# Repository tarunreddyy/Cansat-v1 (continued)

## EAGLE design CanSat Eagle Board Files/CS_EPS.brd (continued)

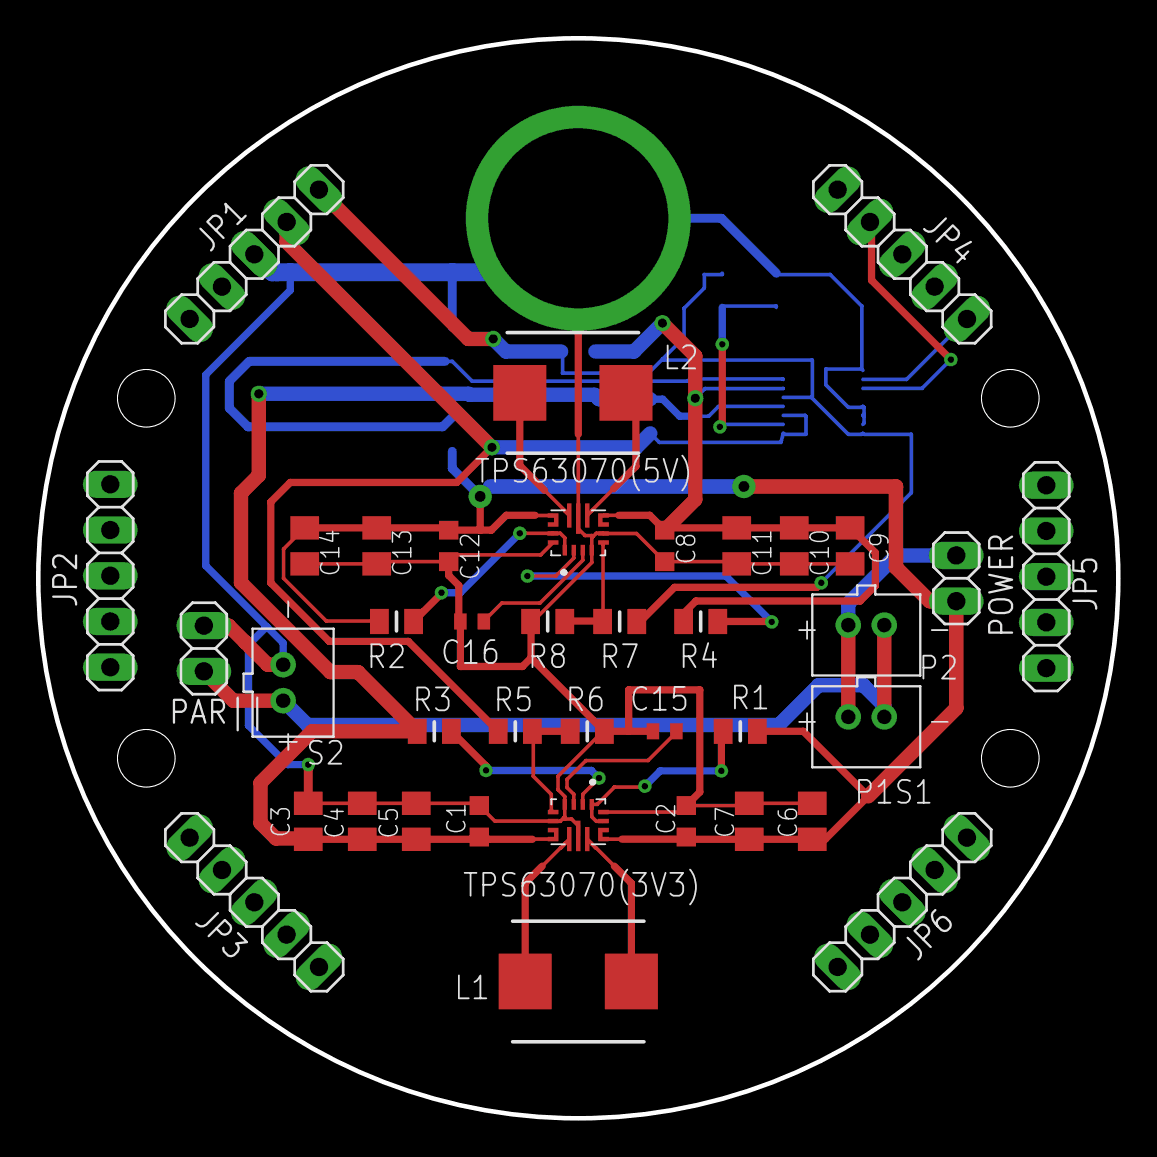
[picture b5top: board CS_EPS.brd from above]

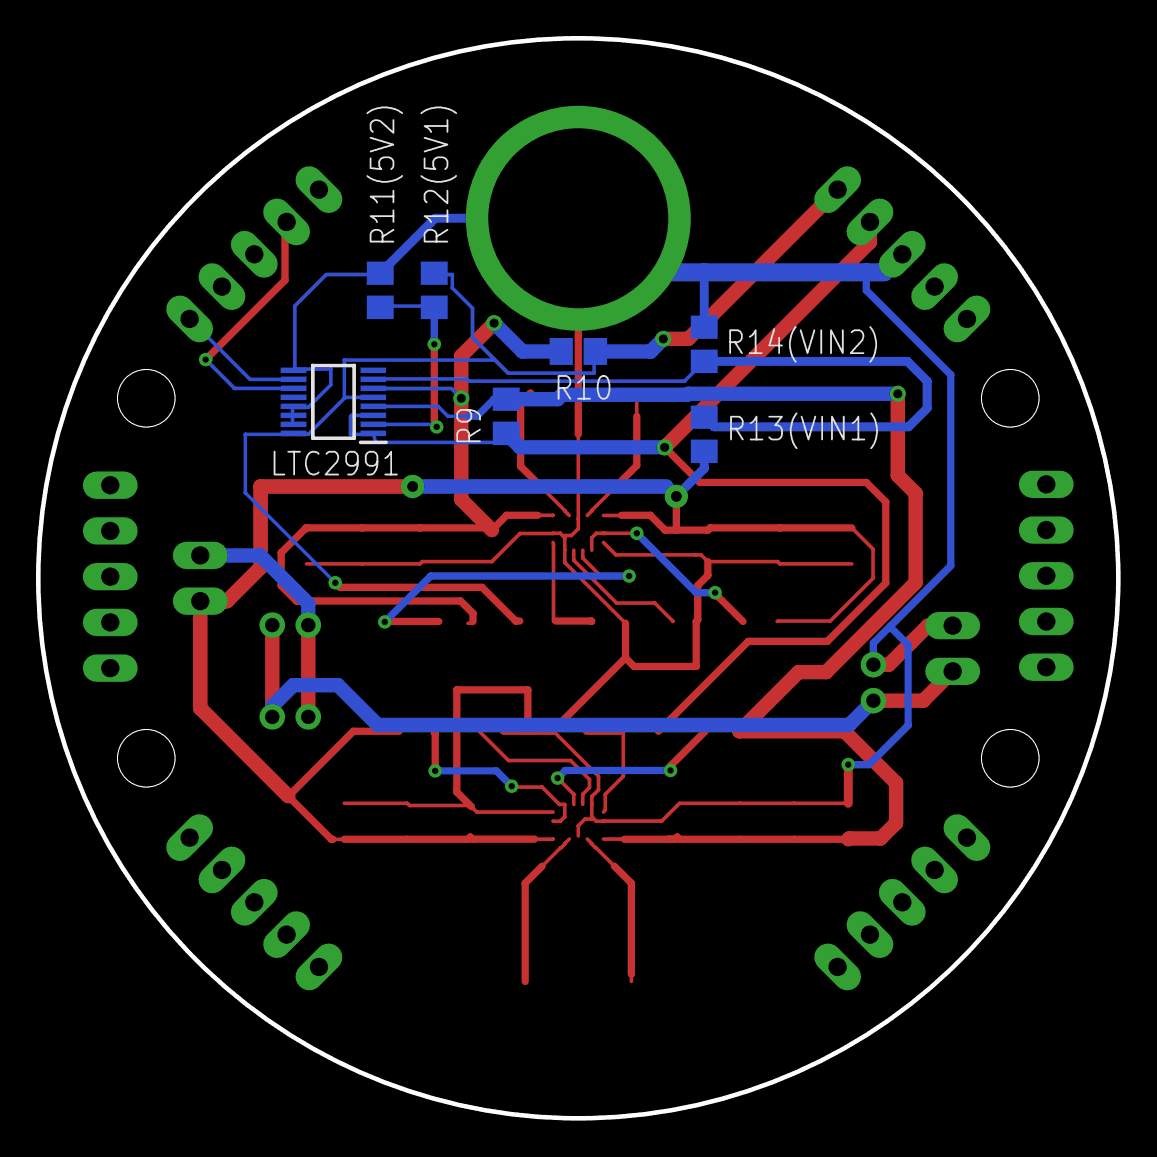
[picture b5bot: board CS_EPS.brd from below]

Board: 2 copper layers, 60.0 x 60.0 mm, 46 parts (7 on the bottom side), 24 nets.

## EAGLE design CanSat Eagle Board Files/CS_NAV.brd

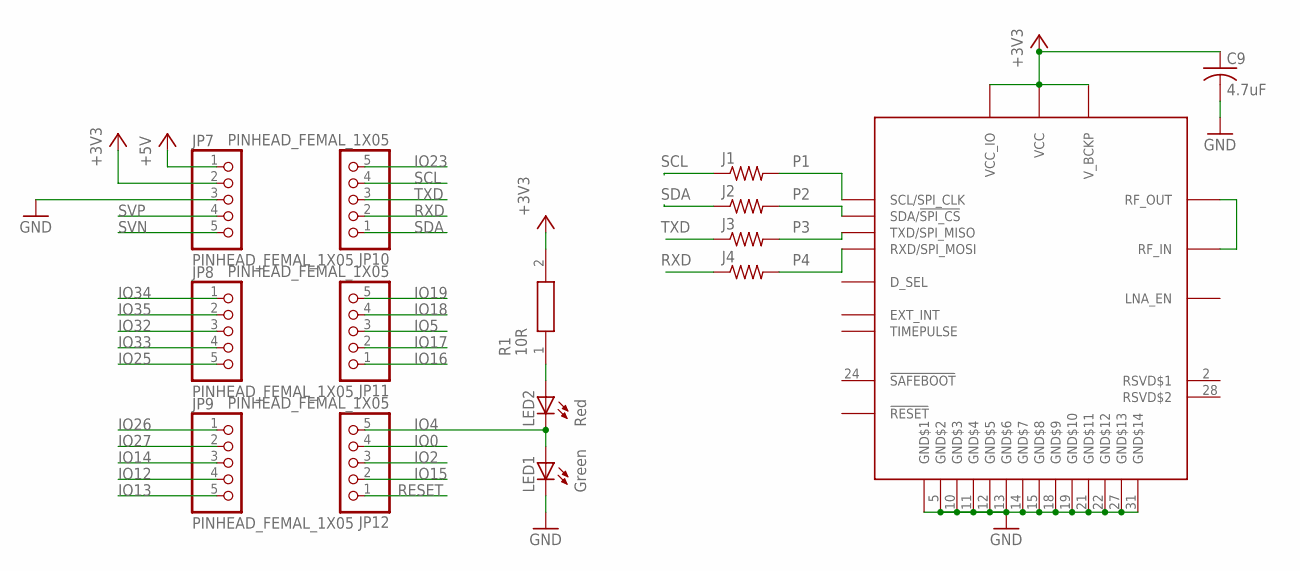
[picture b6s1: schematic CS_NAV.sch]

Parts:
C9: 4.7uF; C0805
CAM-M8C/Q: CAM-M8
J1, J2, J3, J4: R-US_R1206; R1206
JP7, JP8, JP9, JP10, JP11, JP12: PINHEAD_FEMAL_1X05; 1X05F
LED1: Green; CHIPLED_0805
LED2: Red; CHIPLED_0805
R1: 10R; RESC2012X60N

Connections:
+3V3: C9.1, CAM-M8C/Q.1 (VCC_IO), CAM-M8C/Q.8 (V_BCKP), CAM-M8C/Q.9 (VCC), JP7.2, R1.2
+5V: JP7.1
GND: C9.2, CAM-M8C/Q.4 (GND$1), CAM-M8C/Q.5 (GND$2), CAM-M8C/Q.10 (GND$3), CAM-M8C/Q.11 (GND$4), CAM-M8C/Q.12 (GND$5), CAM-M8C/Q.13 (GND$6), CAM-M8C/Q.14 (GND$7), CAM-M8C/Q.15 (GND$8), CAM-M8C/Q.18 (GND$9), CAM-M8C/Q.19 (GND$10), CAM-M8C/Q.21 (GND$11), CAM-M8C/Q.22 (GND$12), CAM-M8C/Q.27 (GND$13), CAM-M8C/Q.31 (GND$14), JP7.3, LED1.C
IO0: JP12.4
IO2: JP12.3
IO4: JP12.5, LED1.A, LED2.C
IO5: JP11.3
IO12: JP9.4
IO13: JP9.5
IO14: JP9.3
IO15: JP12.2
IO16: JP11.1
IO17: JP11.2
IO18: JP11.4
IO19: JP11.5
IO23: JP10.5
IO25: JP8.5
IO26: JP9.1
IO27: JP9.2
IO32: JP8.3
IO33: JP8.4
IO34: JP8.1
IO35: JP8.2
unnamed: CAM-M8C/Q.16 (RF_OUT), CAM-M8C/Q.17 (RF_IN)
unnamed: LED2.A, R1.1
P1: CAM-M8C/Q.6 (SCL/SPI_CLK), J1.2
P2: CAM-M8C/Q.3 (SDA/!SPI_CS), J2.2
P3: CAM-M8C/Q.25 (TXD/SPI_MISO), J3.2
P4: CAM-M8C/Q.26 (RXD/SPI_MOSI), J4.2
RESET: JP12.1
RXD: J4.1, JP10.2
SCL: J1.1, JP10.4
SDA: J2.1, JP10.1
SVN: JP7.5
SVP: JP7.4
TXD: J3.1, JP10.3

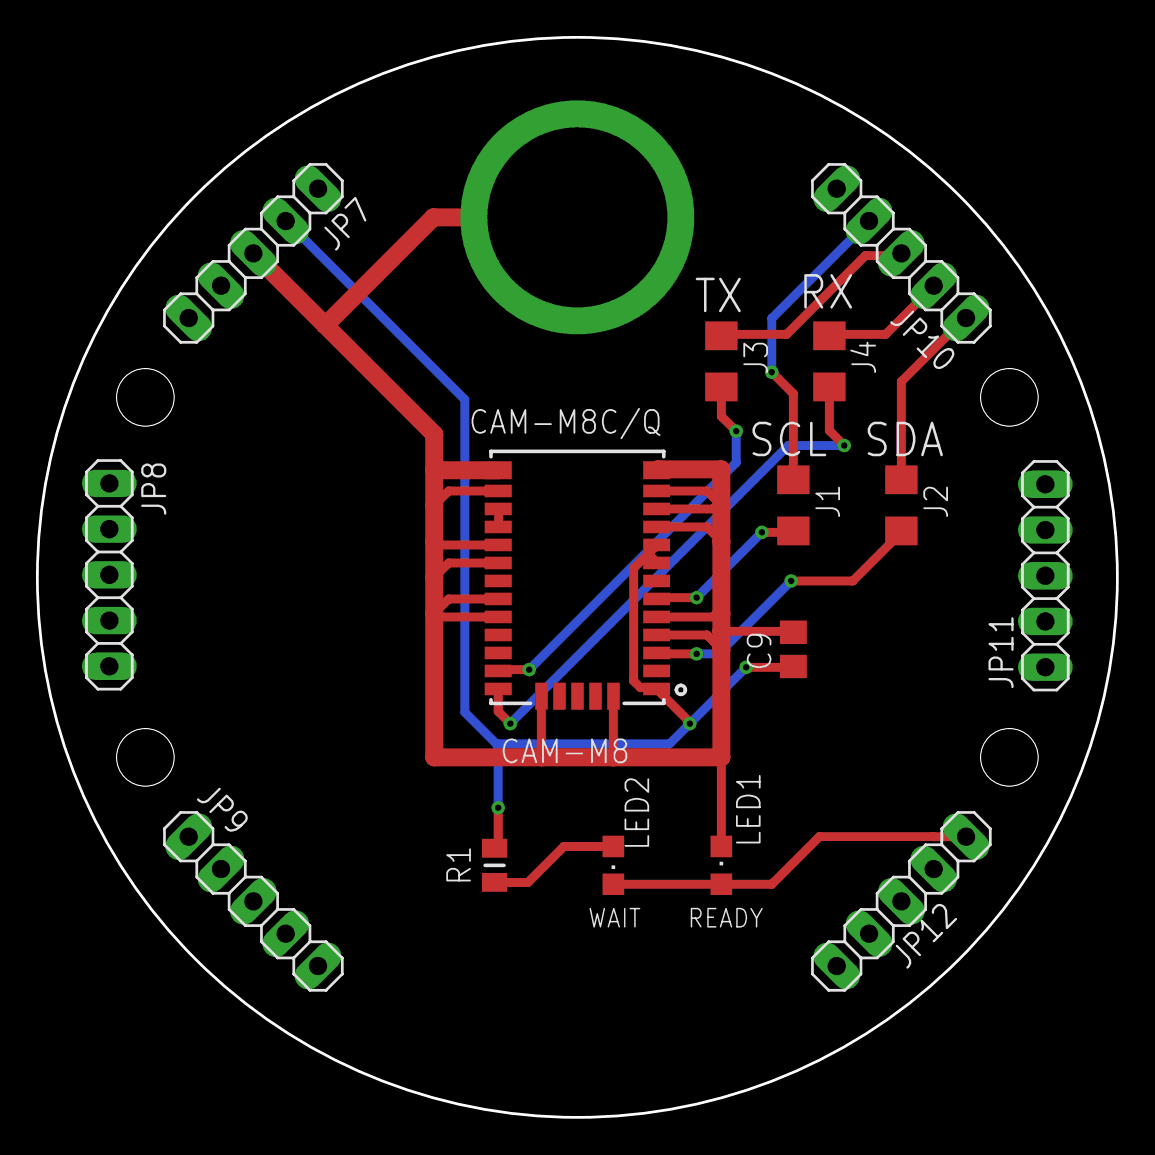
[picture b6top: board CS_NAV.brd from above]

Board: 2 copper layers, 60.0 x 60.0 mm, 15 parts (0 on the bottom side), 13 nets.
